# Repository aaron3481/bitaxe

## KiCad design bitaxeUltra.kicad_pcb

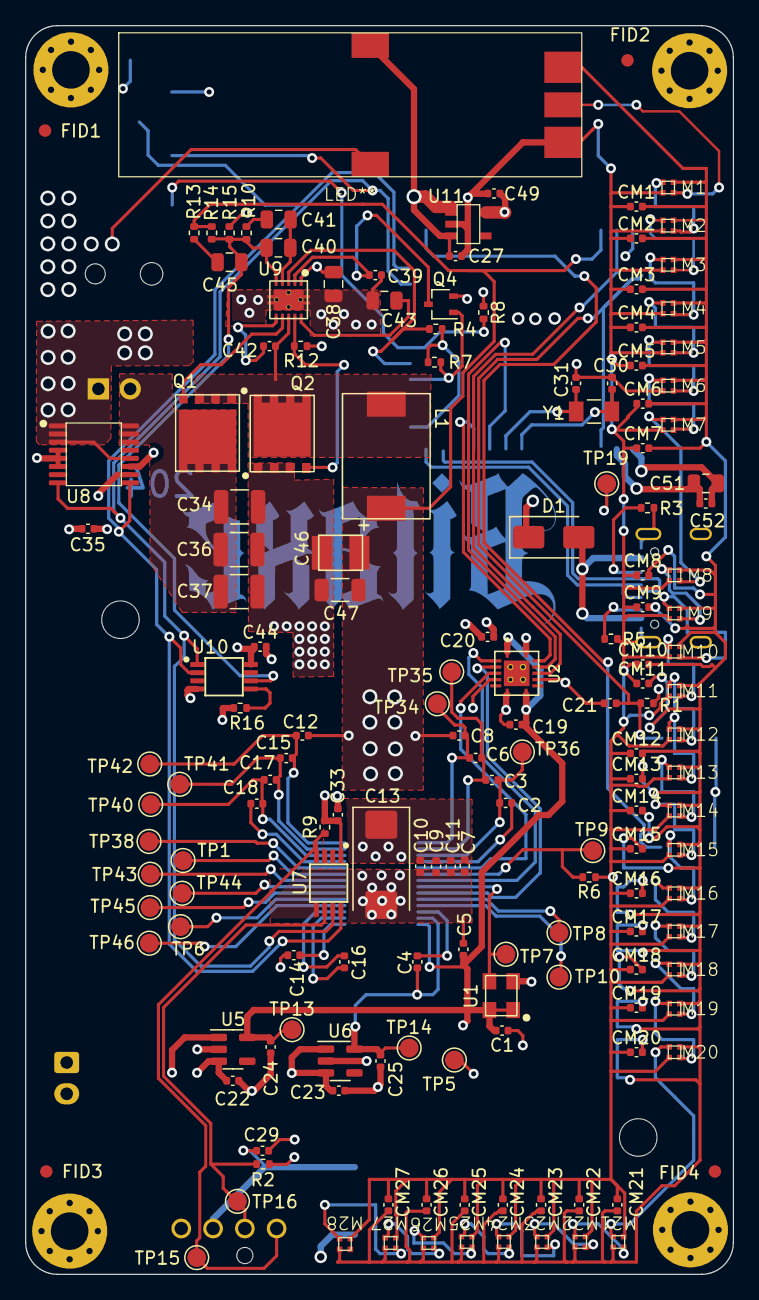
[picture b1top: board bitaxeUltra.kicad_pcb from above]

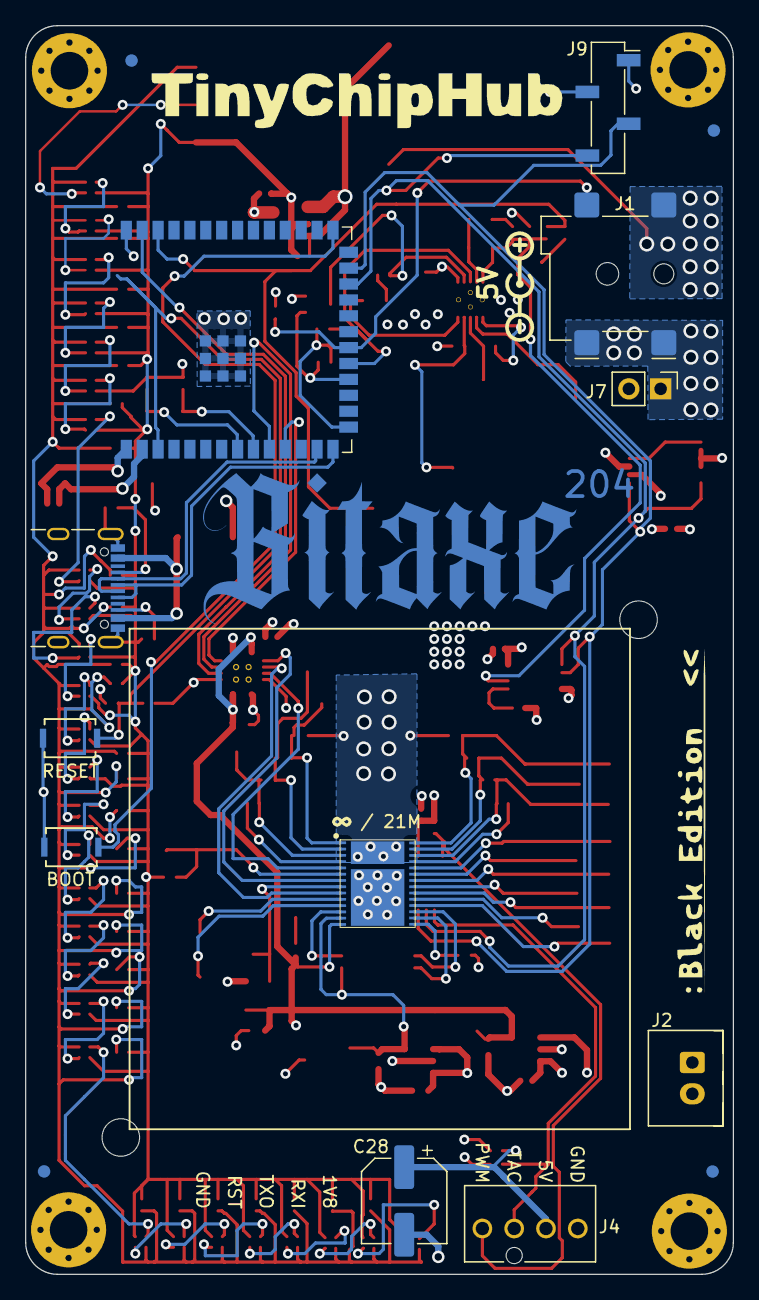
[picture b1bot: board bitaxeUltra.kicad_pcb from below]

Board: 4 copper layers, 56.5 x 99.8 mm, 182 parts (16 on the bottom side), 61 nets.

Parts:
C1, C7, C9, C19, C20, C29, C33, C42, C52: 0.1uF; C_0402_1005Metric
C2, C3, C4, C5, C6, C8, C10, C11, C12, C14, C15, C16, C17, C18, C21, C22, C23, C24, C25, C27, C35, C44, C49: 1uF; C_0402_1005Metric
C13: 330uF; CP_EIA-7343-31_Kemet-D_Pad2.25x2.55mm_HandSolder
C28: 220uF; CP_Elec_6.3x7.7
C30, C31: 6.8pF; C_0402_1005Metric
C34, C36, C37: 47uF; C_1210_3225Metric
C38: 1uF; C_0805_2012Metric
C39: 3.3nF; C_0402_1005Metric
C40: 180pF; C_0805_2012Metric
C41: 1.5nF; C_0805_2012Metric
C43, C51: 10uF; C_0805_2012Metric
C45: 470pF; C_0805_2012Metric
C46: 220uF; CAP_2R5TPE220MAFB
C47: 100uF; C_1206_3216Metric
CM1, CM2, CM3, CM4, CM5, CM6, CM7, CM8, CM9, CM10, CM11, CM12, CM13, CM14, CM15, CM16, CM17, CM18, CM19, CM20, CM21, CM22, CM23, CM24, CM25, CM26, CM27: 0.1uF; C_0402_1005Metric
D1: SS310; D_SMA
FID1, FID2, FID3, FID4, FID5, FID6, FID7, FID8: Fiducial; Fiducial_1mm_Mask2mm
H5, H6: MountingHole; MountingHole_3.5mm
H7, H8, H9, H10: MountingHole_Pad; MountingHole_3mm_Pad_Via
J1: 54-00164; BarrelJack_Wuerth_694106106102_2.0x5.5mm
J2: Conn_01x02; JST_XH_B2B-XH-A_1x02_P2.50mm_Vertical
J4: Conn_01x04; 470531000
J7: Conn_01x02; PinHeader_1x02_P2.54mm_Vertical
J8: USB_C_Receptacle_USB2.0; USB_C_Receptacle_GCT_USB4105-xx-A_16P_TopMnt_Horizontal
J9: Conn_01x04; PinSocket_1x04_P2.54mm_Vertical_SMD_Pin1Right
L1: 150nH; FP1005R1-R15-R
LED**: LED-RF-Controller
M1, M2, M3, M4, M5, M6, M7, M8, M9, M10, M11, M12, M13, M14, M15, M16, M17, M18, M19, M20, M21, M22, M23, M24, M25, M26, M27, M28: XL-1010RGBC
Q1, Q2: CSD17311Q5
Q4: 2N7002K; SOT-323_SC-70
R1, R4, R6, R7, R9: 10k; R_0402_1005Metric
R2: 5.6k; R_0402_1005Metric
R3, R5: 5.1k; R_0402_1005Metric
R8: 1M; R_0402_1005Metric
R10: 3.83k; R_0402_1005Metric
R12: 4.12k; R_0402_1005Metric
R13: 1.33k; R_0402_1005Metric
R14: 4.99k; R_0402_1005Metric
R15: 3.32k; R_0402_1005Metric
R16: 80.6k; R_0402_1005Metric
SW1, SW2: GT-TC029B-H025-L1N; SW_CS1213AGF260_CRS
TP1, TP5, TP6, TP7, TP8, TP9, TP10, TP13, TP14, TP15, TP16, TP19, TP34, TP35, TP36, TP38, TP40, TP41, TP42, TP43, TP44, TP45, TP46: TestPoint; TestPoint_Pad_D1.5mm
U1: 25MHz; O 25,0-JO32-B-1V3-1-T1-LF
U2: TXB0104RGYR; TXB0104
U3: polarity
U5: MCP1824T-1802E; SOT-23-5
U6: MCP1824T-0802E; SOT-23-5
U7: EMC2101; TSSOP-8_3x3mm_P0.65mm
U8: INA260; TSSOP-16_4.4x5mm_P0.65mm
U9: TPS40305
U10: DS4432U+; TSSOP-8_3x3mm_P0.65mm
U11: RT9080-33GJ5
U12: ESP32-S3-WROOM-1
U14: BM1366_mode1; BM1366
Y1: 32.768kHz; SC32S-7PF20PPM

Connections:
/3V3: C20.1, C33.1, C35.1, C44.1, C49.1, C51.1, C52.1, J9.2, R1.1, R2.2, R4.1, R7.1, R8.1, R9.2, TP19.1, U2.14 (VCCB), U7.1 (VDD), U8.10 (VS), U10.8 (VCC), U11.5 (VOUT), U12.2 (3V3), U12.15 (GPIO3/TOUCH3/ADC1_CH2*)
/5V: C22.1, C23.1, C27.1, C28.1, C29.1, C34.1, C36.1, C37.1, C38.1, D1.1, J2.2, J4.2, J7.2, LED**.4, Q1.5 (D), U5.1 (VIN), U5.3 (EN), U6.1 (VIN), U6.3 (EN), U8.14 (IN-), U8.15 (IN-), U8.16 (IN-), U9.1 (VDD), U11.1 (VIN), U11.3 (EN)
/BM1366/0V8: C4.1, C25.1, TP14.1, U6.5 (VOUT), U14.13 (VDDIO_08_0)
/BM1366/1V8: C1.2, C5.1, C19.1, C24.1, TP13.1, U1.1 (EN), U1.4 (VIN), U2.1 (VCCA), U2.8 (OE), U5.5 (VOUT), U14.14 (VDDIO_18_0)
/BM1366/ADDR0: TP8.1, U14.10 (ADDR0)
/BM1366/ADDR1: TP10.1, U14.11 (ADDR1)
/BM1366/BI: R6.2, TP9.1, U14.6 (BI)
/BM1366/BO: TP1.1, U14.23 (BO)
/BM1366/CI: U2.3 (A2), U14.9 (CI)
/BM1366/CLKI: TP7.1, U1.3 (OUT), U14.8 (CLKI)
/BM1366/CLKO: TP44.1, U14.21 (CLKO)
/BM1366/CO: TP45.1, U14.20 (CO)
/BM1366/INV_CLKO: TP6.1, U14.19 (INV_CLKO)
/BM1366/NRSTO: TP38.1, U14.24 (NRSTO)
/BM1366/PIN_MODE: TP46.1, U14.18 (PIN_MODE)
/BM1366/RI: TP43.1, U14.22 (RI)
/BM1366/RO: U2.2 (A1), U14.7 (RO)
/BM1366/RST_N: U2.4 (A3), U14.5 (NRSTI)
/BM1366/VDD1_0: C6.2, C8.1, TP34.1, U14.1 (VDD1_0)
/BM1366/VDD1_1: C12.2, C15.1, TP42.1, U14.28 (VDD1_1)
/BM1366/VDD2_0: C3.2, C6.1, TP35.1, U14.2 (VDD2_0)
/BM1366/VDD2_1: C15.2, C17.1, TP41.1, U14.27 (VDD2_1)
/BM1366/VDD3_0: C2.2, C3.1, TP36.1, U14.3 (VDD3_0)
/BM1366/VDD3_1: C17.2, C18.1, TP40.1, U14.26 (VDD3_1)
/ESP32/EN: C21.1, R1.2, SW1.2, U12.3 (EN)
/ESP32/IO0: SW2.2, U12.27 (GPIO0/BOOT*)
/ESP32/PWR_EN: Q4.1 (G), R7.2, U12.18 (GPIO10/TOUCH10/ADC1_CH9/FSPICS0/FSPIIO4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)
/ESP32/XIN32: C30.1, U12.8 (GPIO15/U0RTS/ADC2_CH4/XTAL_32K_P), Y1.1
/ESP32/XOUT32: C31.1, U12.9 (GPIO16/U0CTS/ADC2_CH5/XTAL_32K_NH5), Y1.2
/Fan/FAN_PWM: J4.4, R9.1, TP15.1, U7.4 (FAN)
/Fan/FAN_TACH: J4.3, R2.1, TP16.1, U7.6 (ALERT/TACH)
/LED/DO: LED**.2, M1.1, M1.4, M2.1, M3.1, M4.1, M5.1, M6.1, M7.1, M8.1, M9.1, M10.1, M11.1, M12.1
/LED/VDD: CM1.2, CM2.2, CM3.2, CM4.2, CM5.2, CM6.2, CM7.2, CM8.2, CM9.2, CM10.2, CM11.2, CM12.2, CM13.2, CM14.2, CM15.2, CM16.2, CM17.2, CM18.2, CM19.2, CM20.2, CM21.2, CM22.2, CM23.2, CM24.2, CM25.2, CM26.2, CM27.2, LED**.1, M1.2, M2.2, M3.2, M4.2, M5.2, M6.2, M7.2, M8.2, M9.2, M10.2, M11.2
/PLUG_SENSE: J1.3, R8.2, U12.20 (GPIO12/TOUCH12/ADC2_CH1/FSPICLK/FSPIIO6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)
/Power/OUT0: C40.2, C45.2, R10.2, R14.2, R15.1, U9.5 (FB), U10.6 (OUT0)
/Power/PGOOD: R4.2, U9.3 (PGOOD), U12.19 (GPIO11/TOUCH11/ADC2_CH0/FSPID/FSPIIO5/S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)
/Power/SW: C42.2, L1.1, Q1.1, Q1.2, Q1.3 (S), Q2.5 (D), U9.8 (SW)
/Power/VIN: J1.1, J7.1, U8.1 (IN+), U8.2 (IN+), U8.3 (IN+), U8.12 (VBUS)
/RST: U2.11 (B3), U12.39 (GPIO1/TOUCH1/ADC1_CH0)
/RX: U2.13 (B1), U12.11 (GPIO18/U1RXD/ADC2_CH7/CLK_OUT3)
/SCL: J9.3, U7.8 (SMCLK), U8.9 (SCL), U10.2 (SCL), U12.25 (GPIO48/SPICLK_N/SUBSPICLK_N_DIFF)
/SDA: J9.4, U7.7 (SMDATA), U8.8 (SDA), U10.1 (SDA), U12.24 (GPIO47/SPICLK_P/SUBSPICLK_P_DIFF)
/TX: U2.12 (B2), U12.10 (GPIO17/U1TXD/ADC2_CH6)
/VDD: C7.1, C8.2, C9.1, C10.1, C11.1, C12.1, C13.1, C46.1, C47.1, L1.2, R13.1, R14.1, U12.38 (GPIO2/TOUCH2/ADC1_CH1), U14.29 (VDD)
GND: C1.1, C2.1, C4.2, C5.2, C7.2, C9.2, C10.2, C11.2, C13.2, C14.2, C16.2, C18.2, C19.2, C20.2, C21.2, C22.2, C23.2, C24.2, C25.2, C27.2, C28.2, C29.2, C30.2, C31.2, C33.2, C34.2, C35.2, C36.2, C37.2, C38.2, C39.2, C43.2, C44.2, C46.2, C47.2, C49.2, C51.2, C52.2, CM1.1, CM2.1, CM3.1, CM4.1, CM5.1, CM6.1, CM7.1, CM8.1, CM9.1, CM10.1, CM11.1, CM12.1, CM13.1, CM14.1, CM15.1, CM16.1, CM17.1, CM18.1, CM19.1, CM20.1, CM21.1, CM22.1, CM23.1, CM24.1, CM25.1, CM26.1, CM27.1, H7.1, H8.1, H9.1, H10.1, J1.2, J2.1, J4.1, J8.A1 (GND), J8.A12 (GND), J8.B1 (GND), J8.B12 (GND), J8.S1 (SHIELD), J9.1, LED**.3, LED**.5, M1.3, M2.3, M3.3, M4.3, M5.3, M6.3, M7.3, M8.3, M9.3, M10.3, M11.3, M12.3, M13.3, M14.3, M15.3, M16.3, M17.3, M18.3, M19.3, M20.3, M21.3, M22.3, M23.3, M24.3, M25.3, M26.3, M27.3, M28.3, Q2.1, Q2.2, Q2.3 (S), Q4.2 (S), R3.1, R5.1, R6.1, R12.2, R15.2, R16.2, SW1.1, SW2.1, TP5.1, U1.2 (GND), U2.5 (A4), U2.7 (GND), U2.10 (B4), U2.15 (GND), U2.16 (GND), U2.17 (GND), U2.18 (GND), U2.19 (GND), U5.2 (GND), U6.2 (GND), U7.5 (GND), U8.4 (A1), U8.5 (A0), U8.6 (GND), U8.11 (GND), U9.11 (GND), U10.4 (GND), U11.2 (GND), U12.1 (GND), U12.40 (GND), U12.41 (GND), U14.4 (VSS), U14.12 (PLL_VSS), U14.17 (VSS), U14.25 (VSS), U14.30 (VSS)
unnamed: C41.2, R10.1
unnamed: C45.1, R13.2
unnamed: D1.2, J8.A4 (VBUS), J8.A9 (VBUS), J8.B4 (VBUS), J8.B9 (VBUS)
unnamed: J8.A5 (CC1), R3.2
unnamed: J8.B5 (CC2), R5.2
unnamed: Q1.4 (G), U9.7 (HDRV)
unnamed: Q2.4 (G), R12.1, U9.9 (LDRV)
unnamed: C39.1, Q4.3 (D), U9.2 (EN/SS)
unnamed: C42.1, U9.6 (BOOT)
unnamed: C43.1, U9.10 (BP)
unnamed: C40.1, C41.1, U9.4 (COMP)
unnamed: R16.1, U10.5 (FS0)
unnamed: J8.A7 (D-), J8.B7 (D-), U12.13 (GPIO19/U1RTS/ADC2_CH8/CLK_OUT2/USB_D-)
unnamed: J8.A6 (D+), J8.B6 (D+), U12.14 (GPIO20/U1CTS/ADC2_CH9/CLK_OUT1/USB_D+)
unnamed: C16.1, U14.16 (VDDIO_08_1)
unnamed: C14.1, U14.15 (VDDIO_18_1)

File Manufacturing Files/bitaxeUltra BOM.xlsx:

Qty | Ref Des | Value | DK | PARTNO | DNP
9 | C1, C7, C9, C19, C20, C29, C33, C42, C52 | 0.1uF | 1292-1639-1-ND | 0402X104K100CT
23 | C2, C3, C4, C5, C6, C8, C10, C11, C12, C14, C15, C16, C17, C18, C21, C22, C23, 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 | 1uF | 587-5514-1-ND | EMK105BJ105MV-F
1 | C13 | 330uF | 718-1028-1-ND | 293D337X9010E2TE3
1 | C28 | 220uF | 732-8422-1-ND | 865080345012
2 | C30, C31 | 6.8pF | 399-C0402C689C5GAC7867CT-ND | C0402C689C5GAC7867
3 | C34, C36, C37 | 47uF | 490-6539-1-ND | GRM32ER61C476KE15L
1 | C38 | 1uF | 1276-6471-1-ND | CL21B105KOFNNNG
1 | C39 | 3.3nF | 1276-1552-1-ND | CL05B332KB5NNNC
1 | C40 | 180pF | 311-1114-1-ND | CC0805JRNPO9BN181
1 | C41 | 1.5nF | 311-1128-1-ND | CC0805KRX7R9BB152
2 | C43, C51 | 10uF | 1276-1096-1-ND | CL21A106KOQNNNE
1 | C45 | 470pF | 1292-1580-1-ND | 0805B471K500CT
1 | C46 | 220uF | P16200CT-ND | 2R5TPE220MAFB
1 | C47 | 100uF | 445-6008-1-ND | C3216X5R0J107M160AB
1 | D1 | SS310 | SK310A-LTPMSCT-ND | SK310A-LTP
1 | J1 | 54-00164 | 839-54-00164CT-ND | 54-00164
1 | J2 | Conn_01x02 | 455-B2B-XH-A-ND | B2B-XH-A
1 | J4 | Conn_01x04 | WM4330-ND | 0470531000
1 | J8 | USB_C_Receptacle_USB2.0 | 2073-USB4105-GF-ACT-ND | USB4105-GF-A
1 | L1 | 150nH | 513-1568-1-ND | FP1005R1-R15-R
2 | Q1, Q2 | CSD17311Q5 | 296-27625-1-ND | CSD17311Q5
1 | Q4 | 2N7002K | 2N7002KWCT-ND | 2N7002KW
5 | R1, R4, R6, R7, R9 | 10k | 311-10KJRCT-ND | RC0402JR-0710KL
1 | R2 | 5.6k | 13-RC0402FR-135K6LCT-ND | RC0402FR-135K6L
2 | R3, R5 | 5.1k | RMCF0402JT5K10CT-ND | RMCF0402JT5K10
1 | R8 | 1M | 311-1.00MLRCT-ND | RC0402FR-071ML
1 | R10 | 3.83k | 311-3.83KLRCT-ND | RC0402FR-073K83L
1 | R11 | 100k | 311-100KJRCT-ND | RC0402JR-07100KL | DNP
1 | R12 | 4.12k | RMCF0402FT4K12CT-ND | RMCF0402FT4K12
1 | R13 | 1.33k | 311-1.33KLRCT-ND | RC0402FR-071K33L
1 | R14 | 4.99k | 311-4.99KLRCT-ND | RC0402FR-074K99L
1 | R15 | 3.32k | 311-3.32KLRCT-ND | RC0402FR-073K32L
1 | R16 | 80.6k | 311-80.6KLRCT-ND | RC0402FR-0780K6L
2 | SW1, SW2 | GT-TC029B-H025-L1N | 2449-CS1213AGF260CT-ND | CS1213AGF260
1 | U1 | 25MHz | 1908-O250-JO32-B-1V3-1-T1-LFCT-ND | O 25,0-JO32-B-1V3-1-T1-LF
1 | U2 | TXB0104RGYR | 296-21930-1-ND | TXB0104RGYR
1 | U5 | MCP1824T-1802E | MCP1824T-1802E/OTCT-ND | MCP1824T-1802E/OT
1 | U6 | MCP1824T-0802E | MCP1824T-0802E/OTCT-ND | MCP1824T-0802E/OT
1 | U7 | EMC2101 | EMC2101-R-ACZL-CT-ND | EMC2101-R-ACZL-TR
1 | U8 | INA260 | 296-45218-5-ND | INA260AIPW
1 | U9 | TPS40305 | 296-37445-1-ND | TPS40305DRCR
1 | U10 | DS4432U+ | DS4432U+-ND | DS4432U+
1 | U11 | RT9080-33GJ5 | 1028-1509-1-ND | RT9080-33GJ5
1 | U12 | ESP32-S3-WROOM-1 | 1965-ESP32-S3-WROOM-1-N16R8CT-ND | ESP32-S3-WROOM-1-N16R8
1 | U14 | BM1366_mode1
1 | Y1 | 32.768kHz | 728-1074-1-ND | SC32S-7PF20PPM
28 | M1,M2,M3,M4,M5,M6,M7,M8,M9,M10,M11,M12,M13,M14,M15,M16,M17,M18,M19,M20,M21,M22,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 |  | XL-1010RGBC-WS2812B | XL-1010RGBC-WS2812B
27 | CM1,CM2,CM3,CM4,CM5,CM6,CM7,CM8,CM9,CM10,CM11,CM12,CM13,CM14,CM15,CM16,CM17,CM1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 | 0.1uF |  | VJ0402G104KXQCW1BC

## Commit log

2024-01-08 add fill
2024-03-21 Add LED-RF-Controller.kicad_mod
2024-03-21 Init commit to TCH-204 Black edition with LED lights
2024-03-21 Finish LED layout. Can pass to factory for prototype test
2024-03-21 Add Black Edition logo
2024-04-06 Fix Led wiring issue
2024-04-16 Finalize RGBitaxe
2024-04-16 Upload gerbers files
